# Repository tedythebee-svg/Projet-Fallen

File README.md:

# Projet Fallen
 My project is named, Deskbuddy because I wanted to do a desk companion. I am a begginer.
 So I used AI but not to do my job, my principal objective is to learn electronics and have fun
 My project is using an ESP32-S3-WROOM-1-N16R8, 2 buttons for reset and boot, a led to have a diagnostic etc... (to see every component exactly, look in the BOM)
 To see the schematics and PCB screenshots, look in the Sreenshots.

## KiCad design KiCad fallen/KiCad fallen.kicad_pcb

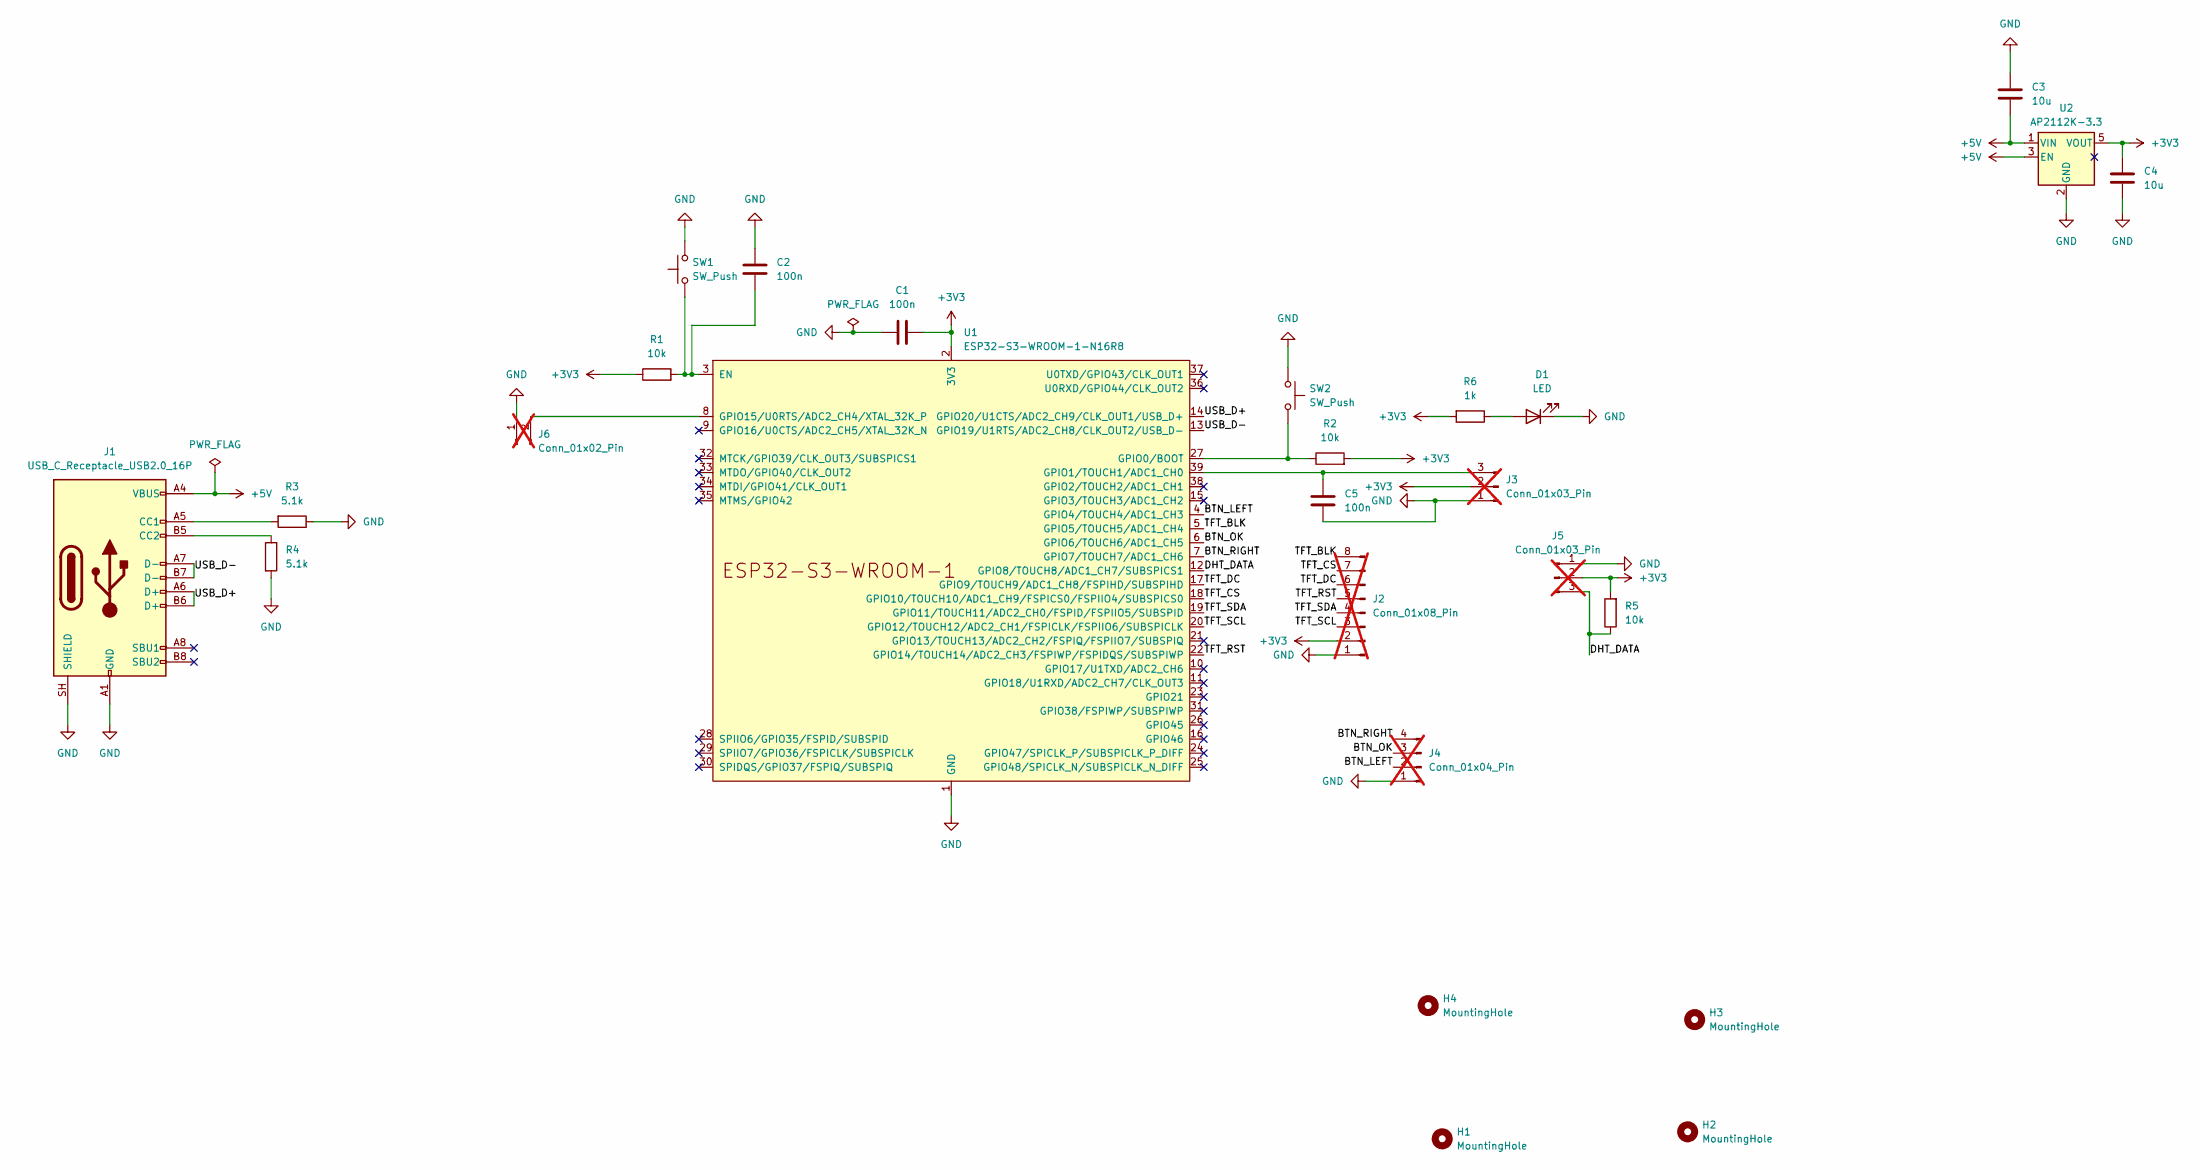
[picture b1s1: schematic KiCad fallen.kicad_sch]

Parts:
C1, C2, C5: 100n; C_0805_2012Metric; LCSC C49678
C3, C4: 10u; C_0805_2012Metric; LCSC C15850
D1: LED; LED_0805_2012Metric; LCSC C2297
H1, H2, H3, H4: MountingHole; MountingHole_3.2mm_M3
J1: USB_C_Receptacle_USB2.0_16P; USB_C_Receptacle_GCT_USB4105-xx-A_16P_TopMnt_Horizontal; LCSC C2765186
J2: Conn_01x08_Pin; PinHeader_1x08_P2.54mm_Vertical; not fitted
J3, J5: Conn_01x03_Pin; PinHeader_1x03_P2.54mm_Vertical; not fitted
J4: Conn_01x04_Pin; PinHeader_1x04_P2.54mm_Vertical; not fitted
J6: Conn_01x02_Pin; PinHeader_1x02_P2.54mm_Vertical; not fitted
R1, R2, R5: 10k; R_0805_2012Metric; LCSC C17414
R3, R4: 5.1k; R_0805_2012Metric; LCSC C27834
R6: 1k; R_0805_2012Metric; LCSC C17513
SW1, SW2: SW_Push; SW_SPST_TL3342; LCSC C318884
U1: ESP32-S3-WROOM-1-N16R8; ESP32-S3-WROOM-1; LCSC C2913202
U2: AP2112K-3.3; SOT-23-5; LCSC C51118

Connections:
+3V3: C1.2, C4.1, J2.2, J3.2, J5.2, R1.1, R2.2, R5.2, R6.2, U1.2 (3V3), U2.5 (VOUT)
+5V: C3.2, J1.A4 (VBUS), J1.A9 (VBUS), J1.B4 (VBUS), J1.B9 (VBUS), U2.1 (VIN), U2.3 (EN)
/BTN_LEFT: J4.2, U1.4 (GPIO4/TOUCH4/ADC1_CH3)
/BTN_OK: J4.3, U1.6 (GPIO6/TOUCH6/ADC1_CH5)
/BTN_RIGHT: J4.4, U1.7 (GPIO7/TOUCH7/ADC1_CH6)
/DHT_DATA: J5.3, R5.1, U1.12 (GPIO8/TOUCH8/ADC1_CH7/SUBSPICS1)
/TFT_BLK: J2.8, U1.5 (GPIO5/TOUCH5/ADC1_CH4)
/TFT_CS: J2.7, U1.18 (GPIO10/TOUCH10/ADC1_CH9/FSPICS0/FSPIIO4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)
/TFT_DC: J2.6, U1.17 (GPIO9/TOUCH9/ADC1_CH8/FSPIHD/SUBSPIHD)
/TFT_RST: J2.5, U1.22 (GPIO14/TOUCH14/ADC2_CH3/FSPIWP/FSPIDQS/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)
/TFT_SCL: J2.3, U1.20 (GPIO12/TOUCH12/ADC2_CH1/FSPICLK/FSPIIO6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)
/TFT_SDA: J2.4, U1.19 (GPIO11/TOUCH11/ADC2_CH0/FSPID/FSPIIO5/S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)
/USB_D+: J1.A6 (D+), J1.B6 (D+), U1.14 (GPIO20/U1CTS/ADC2_CH9/CLK_OUT1/USB_D+)
/USB_D-: J1.A7 (D-), J1.B7 (D-), U1.13 (GPIO19/U1RTS/ADC2_CH8/CLK_OUT2/USB_D-)
GND: C1.1, C2.1, C3.1, C4.2, C5.2, D1.1 (K), J1.A1 (GND), J1.A12 (GND), J1.B1 (GND), J1.B12 (GND), J1.SH (SHIELD), J2.1, J3.1, J4.1, J5.1, J6.1, R3.1, R4.2, SW1.2, SW2.1, U1.1 (GND), U1.40 (GND), U1.41 (GND), U2.2 (GND)
unnamed: D1.2 (A), R6.1
unnamed: J1.A5 (CC1), R3.2
unnamed: J1.B5 (CC2), R4.1
unnamed: C5.1, J3.3, U1.39 (GPIO1/TOUCH1/ADC1_CH0)
unnamed: J6.2, U1.8 (GPIO15/U0RTS/ADC2_CH4/XTAL_32K_P)
unnamed: C2.2, R1.2, SW1.1, U1.3 (EN)
unnamed: R2.1, SW2.2, U1.27 (GPIO0/BOOT)

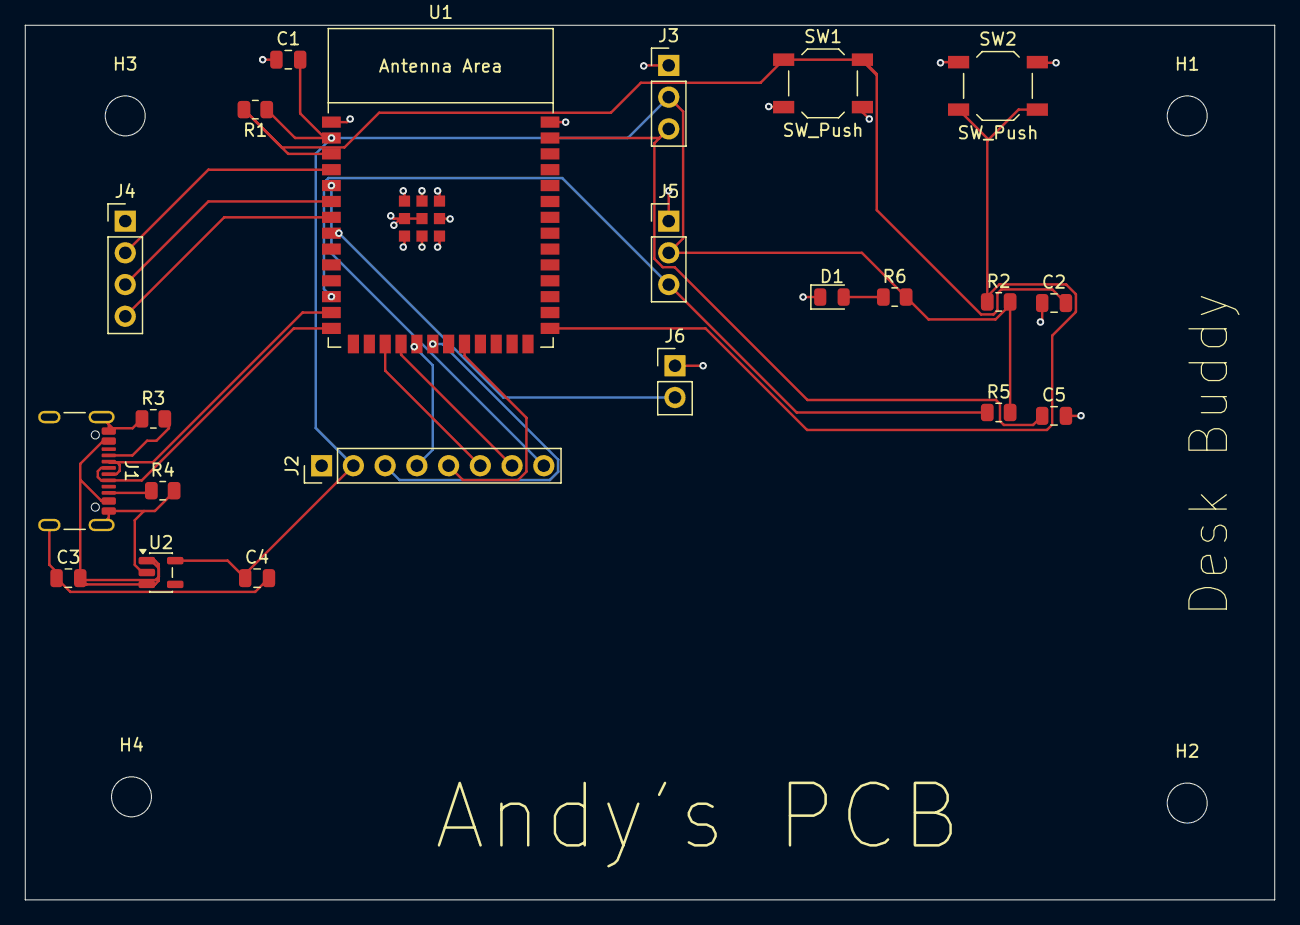
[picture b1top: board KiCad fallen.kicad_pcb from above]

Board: 2 copper layers, 100.0 x 70.0 mm, 26 parts (0 on the bottom side), 22 nets.

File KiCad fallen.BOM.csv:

"Id";"Designator";"Footprint";"Quantity";"Designation";"Supplier and ref";
1;"C1, C2, C5";"C_0805_2012Metric";3;"100n";;;
2;"C3, C4";"C_0805_2012Metric";2;"10u";;;
3;"D1";"LED_0805_2012Metric";1;"LED";;;
4;"J1";"USB_C_Receptacle_GCT_USB4105-xx-A_16P_TopMnt_Horizontal";1;"USB_C_Receptacle_USB2.0_16P";;;
5;"J2";"PinHeader_1x08_P2.54mm_Vertical";1;"Conn_01x08_Pin";;;
6;"J3, J5";"PinHeader_1x03_P2.54mm_Vertical";2;"Conn_01x03_Pin";;;
7;"J4";"PinHeader_1x04_P2.54mm_Vertical";1;"Conn_01x04_Pin";;;
8;"J6";"PinHeader_1x02_P2.54mm_Vertical";1;"Conn_01x02_Pin";;;
9;"R1, R2, R5";"R_0805_2012Metric";3;"10k";;;
10;"R3, R4";"R_0805_2012Metric";2;"5.1k";;;
11;"R6";"R_0805_2012Metric";1;"1k";;;
12;"SW1, SW2";"SW_SPST_TL3342";2;"SW_Push";;;
13;"U1";"ESP32-S3-WROOM-1";1;"ESP32-S3-WROOM-1-N16R8";;;
14;"U2";"SOT-23-5";1;"AP2112K-3.3";;;
